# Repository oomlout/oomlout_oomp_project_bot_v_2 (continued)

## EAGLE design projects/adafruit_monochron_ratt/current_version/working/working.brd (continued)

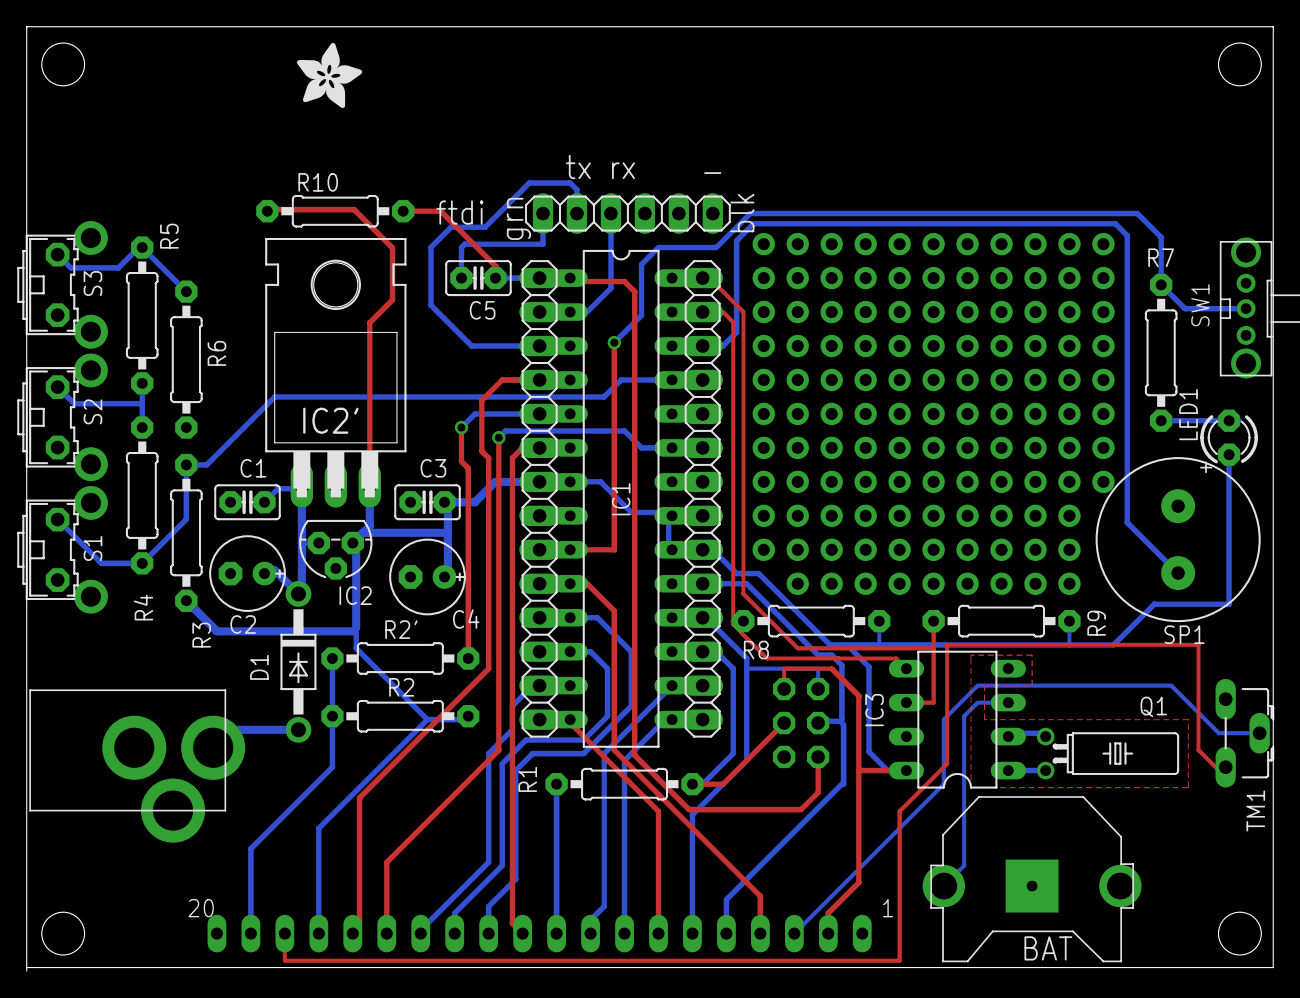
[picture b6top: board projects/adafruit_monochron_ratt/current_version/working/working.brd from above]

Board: 2 copper layers, 93.2 x 70.4 mm, 37 parts (1 on the bottom side), 38 nets.

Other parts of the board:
U$2: ADAFRUIT_5MM

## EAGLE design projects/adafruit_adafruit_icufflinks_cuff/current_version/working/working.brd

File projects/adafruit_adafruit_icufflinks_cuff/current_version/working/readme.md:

# adafruit_icufflinks
 
## summary 
* id: adafruit_adafruit_icufflinks_cuff
* user: adafruit
* name: adafruit_icufflinks
* board: cuff
* repo: https://github.com/adafruit/Adafruit_iCufflinks

* src_file_repo_sch: 
* src_file_repo_sch_link: https://github.com/adafruit/Adafruit_iCufflinks/tree/master/
* full details link: https://github.com/oomlout/oomlout_oomp_project_bot_v_2/tree/main/projects/adafruit_adafruit_icufflinks_cuff/current_version/working  

## pcb  

[board (pdf)](working.pdf)

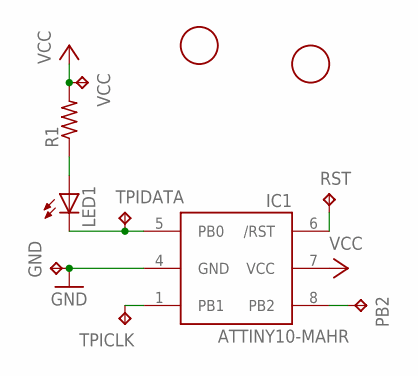
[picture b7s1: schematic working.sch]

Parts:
GND: TPTP10R; TP10R
IC1: ATTINY10-MAHR; UDFN-8
LED1: LEDSMLK34; SMLK34
PB2: TPTP10R; TP10R
R1: R-US_R0805; R0805
RST: TPTP10R; TP10R
TPICLK: TPTP10R; TP10R
TPIDATA: TPTP10R; TP10R
U$2, U$3: FIDUCIAL; FIDUCIAL_1MM
VCC: TPTP10R; TP10R

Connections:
B0: IC1.5 (PB0), LED1.K (C), TPIDATA.TP
B1: IC1.1 (PB1), TPICLK.TP
B2: IC1.8 (PB2), PB2.TP
GND: GND.TP, IC1.4 (GND)
unnamed: LED1.A, R1.1
RST: IC1.6 (/RST), RST.TP
VCC: IC1.7 (VCC), R1.2, VCC.TP

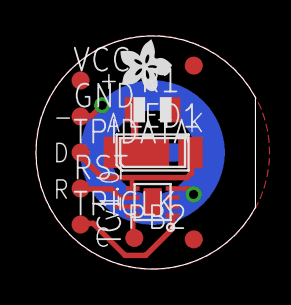
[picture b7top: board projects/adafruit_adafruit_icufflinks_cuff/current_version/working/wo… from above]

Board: 2 copper layers, 12.2 x 12.9 mm, 12 parts (0 on the bottom side), 7 nets.

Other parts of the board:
U$1: ADAFRUIT200MIL

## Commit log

2023-09-07 comitting after 1 generations
2023-09-07 working on code
2023-09-07 more eagle to kicad
2023-09-08 all brought together
2023-09-09 project generations
2023-09-09 Updating readmes and images
2023-09-09 comitting after 100 generations
2023-09-10 new readmes and image resolutions.
2023-09-10 position test
2023-09-10 added mounting holes
2023-09-10 readme fix
2023-09-10 getting up to date
2023-09-13 added generate doc
2023-09-13 first run through
2023-09-14 some workings.
2023-09-15 comitting after 200 generations
2023-09-22 some works
2023-10-08 working on gens
